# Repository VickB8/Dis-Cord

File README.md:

# Dis-Cord
Custom 6-key macro pad powered by a XIAO RP2040 with a 0.91 inch OLED display. Includes Fusion 360, Chrome, KiCad, Valorant, YouTube, and Arduino IDE shortcuts, plus a rotary encoder for volume control and an OLED display. Pressing the encoder switches to a Discord layer with controls for mute, deafen, screen sharing, and other Discord shortcuts.

# Inspiration

I wanted to make a custom macro pad that I could actually use while working on my computer. Instead of making all of the keys do the same type of shortcut. I wanted each key to have a different purpose depending on what i am doing.

I also wanted the hack pad to have more functionality than just six buttons, so I added a rotary encoder for volume control and an OLED display to show the current mode and volume.

The main ideas was to have one layer for my normal computer shortcuts and another layer specifically for discord.

# Design Concept

I wanted the hackpad to be more than just a small PCB with switches on it, so I designed the physical setup around how I would actually use it at my desk.

I made an under-desk stand that holds the hackpad at an angle, making the keys easy to reach while keeping the OLED visible. The stand is designed to attach underneath the desk so the hackpad sticks out slightly instead of taking up space on the desk.

I also added a dedicated space for a flexible LED filament. I chose a flexible LED because it can follow the shape of the enclosure and add lighting without needing individual LEDs placed around the case. The lighting is mainly a visual design element and is integrated into the physical design of the hackpad.

# How it Works

The hackpad uses a Seeed Studio RP2040 as the main microcontroller.

The six mechanical switches act as USB Keyboard inputs. When a key is presses, the XIAO RP2040 sends the programmed keyboard shortcute to the computer.

The rotary encoder controls the computer volume. Pressing the encoder button changes the hack pad from the m=normal mode to Discord mode.

The OLED Display shows the current mode and volume percentage so I can see what the hackpad is doing without needing to look at the computer.

# Normal Mode

The normal mode is designed around programs and actions I commonly use.

SW1      Fusion 360          SW4      Valorant
SW2      New Chrome tab      SW5      Youtube
SW3      KiCad               SW6      Arduino IDE
Rotary Encoder Volume Up/Down
Encoder Button Switch to Discord Mode.

The six keys are programmed as shortcuts for quickly opening or switching to these programs and actions.

# Discord Mode

Pressing the rotary encoder button switches the hackpad into the Discord layer.

In this mode, the six keys are changed to Discord controls so the same physical buttons can be used for completely different functions.

SW1      Mute                  SW4      Toggle Video
SW2      Deafen                SW5      Discord Shortcut
SW3      Toggle Screen Share   SW6      Discord Shortcut
Rotary Encoder Volume Up/Down
Encoder Button Switch to Discord Mode.

This allows hack pad to have more functions without needing to add more physical buttons.

# OLED Display

The 0.9 inch OLED is used as a status display

It shows information such as:

Current Mode
Normal Mode / Discord Mode
Current Volume percentage

The display changes when the encoder button is pressed so it is easy to tell which set of functions the keys are currently using.

# Rotary Encoder

The Rotary Encoder has two main functions

Turning the Encoder

Turn clockwise - Increase Volume
Turn antiClockwise - Decrease Volume

Pressing the Encoder

Normal Mode - Discord Mode
Discord Mode - Normal Mode

This gives the Hack pas a simple way to switch between two different sets of controls.

# Challenges

One of the biggest challenges was figuring out how to fit six switches, a rotary encoder and an OLED display into a compact design while still making everything comfortable to use.

I also had to figure out how the XIAO RP2040 GPIO pins would be assigned to each component and make sure the schematic and PCB matched the firmware.

Another challenge was getting the rotary encoder to work correctly for both volume control and mode switching.

Designing the PCB in KiCad also took some troubleshooting, especially when working with footprints, silkscreen and the physical placement of the components.

The enclosure was another part of the project that required adjustments. I had to design the case around the actual PCB and components instead of treating the enclosure as a separate part.

What I Learned
How to design a custom PCB in KiCad
How to use the XIAO RP2040
How USB HID keyboard input works
How to program mechanical keyboard switches
How rotary encoders work
How to use an OLED display
How to create multiple keyboard layers
How to send keyboard shortcuts from a microcontroller
How to design a 3D-printed enclosure around a PCB
How to use KiCad DRC to check a PCB
How hardware and firmware have to work together

# Components

1x Seeed Studio XIAO RP2040
6x MX-style mechanical keyboard switches
6x White blank DSA keycaps
1x Rotary encoder
1x 0.9 inch OLED display
Custom PCB
Connecting wires
3D-printed enclosure
M3 hardware

# PCB

The PCB was designed in KiCad and connects the XIAO RP2040 to the six switches, rotary encoder and OLED display.

The component placement was designed around the physical layout of the final hackpad.

# Schematic

The schematic shows the electrical connections between the XIAO RP2040 and the different inputs and display components.

# Case Design

The enclosure was designed specifically for the PCB and components.

I wanted the final design to look more like a finished product instead of just a PCB with switches attached to it. The case holds the electronics while keeping the switches, rotary encoder and OLED accessible.

For assembling the case, I used 5 mm M3 screws instead of the provided 16 mm M3 screws. The shorter screws worked better with my enclosure design and were enough to securely hold the parts together and have some space for the desk mount to easily slide in from the bottom 

# Under-Desk Stand

I designed a custom stand for mounting the hackpad underneath my desk.

The stand positions the hackpad at roughly a 40-degree angle so the buttons are easy to press and the OLED screen can still be seen while sitting at the desk.

Mounting it underneath the desk also keeps the main desk surface clear while making the hackpad easy to access.

# Flexible LED

I also designed a dedicated space in the enclosure for a flexible LED filament.

I chose a flexible LED instead of using individual LEDs because it can bend around the shape of the design and give the hackpad a cleaner appearance.

The LED is integrated into the enclosure so it becomes part of the physical design rather than having separate LEDs mounted around the PCB.

# Firmware

The firmware is written in Arduino/C++ and runs on the XIAO RP2040.

It handles:

Six mechanical switches
Rotary encoder input
Volume control
OLED display
Normal keyboard layer
Discord keyboard layer
Mode switching
USB HID keyboard commands

The firmware allows the same physical buttons to perform different actions depending on the current mode.

# Software

Arduino IDE
Arduino/C++
USB HID keyboard functionality
OLED display libraries

# Features

6 programmable mechanical keys
XIAO RP2040 microcontroller
Rotary encoder
Computer volume control
0.9 inch OLED display
Two different control layers
Discord control layer
USB HID keyboard functionality
Custom PCB
Custom 3D-printed enclosure
Custom key layout

# Design Files

The repository contains the files for the different parts of the project including:

KiCad schematic
KiCad PCB
PCB design files
3D enclosure files
Firmware
Project images

# Final Result

The finished hackpad combines the PCB, firmware, switches, OLED and enclosure into one device.

## BOM (Bill of Materials)

Here is everything needed to build the Dis-Cord hackpad.

| Component | Quantity | Purchase Link |
|---|---:|---|
| Seeed XIAO RP2040 | 1 | [AliExpress](https://www.aliexpress.com/w/wholesale-see​​ed-studio-xiao-rp2040.html) |
| WS2812B LEDs | 2 | [DigiKey](https://www.digikey.ca/en/products/filter/led-addressable-specialty/126) |
| Cherry MX Switches | 4 | [Amazon](https://www.amazon.ca/s?k=cherry+mx+switches) |
| DSA Keycaps | 4 | [Amazon](https://www.amazon.ca/s?k=DSA+keycaps) |
| Rotary Encoder | 1 | [Amazon](https://www.amazon.ca/s?k=EC11+rotary+encoder) |
| 0.91-inch OLED | 1 | [Amazon](https://www.amazon.ca/s?k=0.91+OLED+SSD1306) |
| 1N4148 Diodes | 5 | [Buy here](https://www.amazon.ca/s?k=1N4148+diodes) |
| M3x5x4 Heat-set Inserts | 5 | [Amazon](https://www.amazon.ca/s?k=M3x5x4+heat+set+inserts) |
| M3x16mm Screws | 3 | [Amazon](https://www.amazon.ca/s?k=M3x16+screws) |
| M3x12mm Screws | 2 | [Amazon](https://www.amazon.ca/s?k=M3x12+screws) |
| Custom PCB | 1 | [JLCPCB](https://jlcpcb.com/) |

## Tools Required

| Tool | Quantity | Purchase Link |
|---|---:|---|
| Soldering Kit | 1 | [Amazon Canada](https://www.amazon.ca/dp/B0DT437CP4) |

## Total Project Cost

*Prices are approximate averages in CAD and may vary by supplier.*

| Item | Quantity | Estimated Cost (CAD) |
|---|---:|---:|
| Seeed XIAO RP2040 | 1 | $12.00 |
| Cherry MX Switches | 4 | $4.00 |
| DSA Keycaps | 4 | $6.00 |
| Rotary Encoder | 1 | $4.00 |
| 0.91-inch OLED Display | 1 | $7.00 |
| 1N4148 Diodes | 5 | $1.00 |
| WS2812B LEDs | 2 | $2.00 |
| M3x5x4 Heat-set Inserts | 5 | $1.00 |
| M3x16mm Screws | 3 | $0.50 |
| M3x12mm Screws | 2 | $0.50 |
| Custom PCB | 1 | $10.00 |
| **Estimated Component Total** | | **$48.00** |
| Soldering Kit (reusable tool) | 1 | $25.00 |
| **Estimated Total Including Tools** | | **$73.00** |

*Note: These are approximate component-use costs. Hardware may be sold in multipacks, and the actual checkout total can be higher due to minimum order quantities, shipping, and taxes. The soldering kit is reusable and is not included in the component total.*

## Extra Stuff

- USB cable for connecting the macropad to a computer
- Soldering iron and solder for assembly
- 3D printer for the enclosure and mounting stand

The main goal of the project was to make something that was both useful and custom instead of just making a basic macro pad. The two-layer system lets me use the same six buttons for normal computer shortcuts and Discord controls.

This project helped me learn more about PCB design, embedded programming, USB HID, OLED displays, rotary encoders and designing physical enclosures for electronics.

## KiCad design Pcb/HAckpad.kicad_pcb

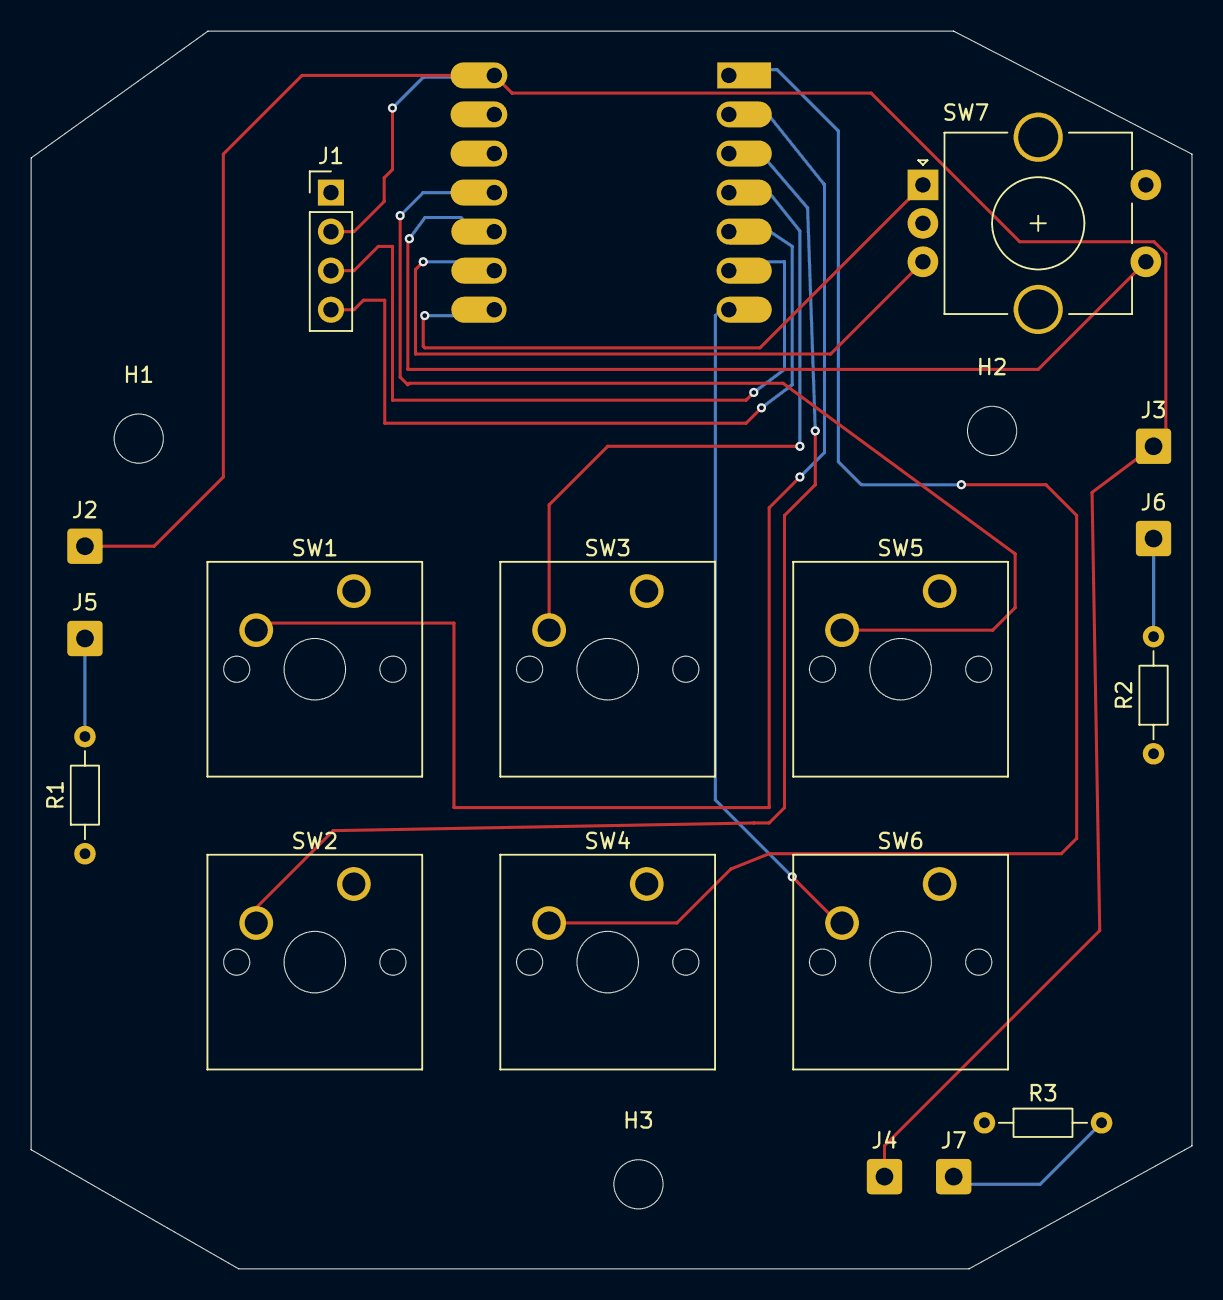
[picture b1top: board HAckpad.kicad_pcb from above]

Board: 2 copper layers, 75.5 x 80.5 mm, 21 parts (1 on the bottom side), 16 nets.

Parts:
H1, H2, H3: MountingHole; MountingHole_3.2mm_M3
J1: Conn_01x04_Socket; PinHeader_1x04_P2.54mm_Vertical
J2, J3, J4, J5, J6, J7: Conn_01x01; SolderWire-0.5sqmm_1x01_D0.9mm_OD2.3mm
R1, R2, R3: R; R_Axial_DIN0204_L3.6mm_D1.6mm_P7.62mm_Horizontal
SW1, SW2, SW3, SW4, SW5, SW6: SW_Push; SW_Cherry_MX_1.00u_PCB
SW7: RotaryEncoder_Switch; RotaryEncoder_Alps_EC11E-Switch_Vertical_H20mm_CircularMoun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
U1: MOUDLE-SEEEDUINO-XIAO; XIAO-Generic-Hybrid-14P-2.54-21X17.8MM

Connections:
GND: J1.1, R1.1, R2.1, R3.1, SW1.1, SW2.1, SW3.1, SW4.1, SW5.1, SW6.1, SW7.C, SW7.S2
unnamed: J1.2, J2.1 (Pin_1_1), J3.1 (Pin_1_1), J4.1 (Pin_1_1), U1.14 (5V)
unnamed: J1.3, U1.6 (PA9_A5_D5_SCL)
unnamed: J1.4, U1.5 (PA8_A4_D4_SDA)
unnamed: J5.1 (Pin_1_1), R1.2
unnamed: J6.1 (Pin_1_1), R2.2
unnamed: J7.1 (Pin_1_1), R3.2
unnamed: SW4.2, U1.1 (PA02_A0_D0)
unnamed: SW1.2, U1.2 (PA4_A1_D1)
unnamed: SW7.S1, U1.10 (PA5_A9_D9_MISO)
unnamed: SW5.2, U1.11 (PA6_A10_D10_MOSI)
unnamed: SW7.B, U1.9 (PA7_A8_D8_SCK)
unnamed: SW2.2, U1.3 (PA10_A2_D2)
unnamed: SW3.2, U1.4 (PA11_A3_D3)
unnamed: SW6.2, U1.7 (PB08_A6_D6_TX)
unnamed: SW7.A, U1.8 (PB09_A7_D7_RX)
